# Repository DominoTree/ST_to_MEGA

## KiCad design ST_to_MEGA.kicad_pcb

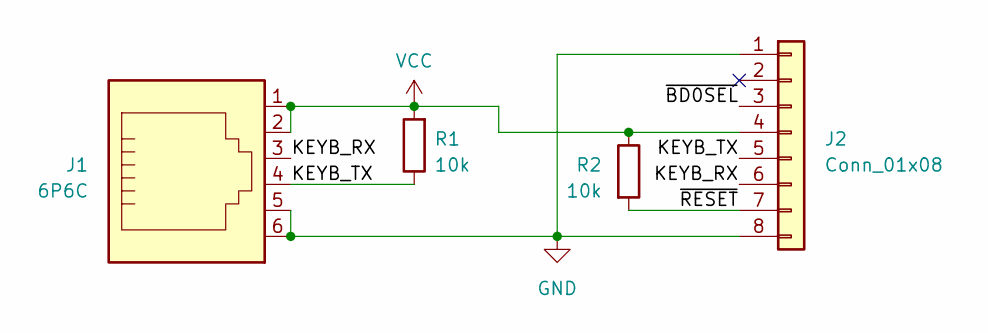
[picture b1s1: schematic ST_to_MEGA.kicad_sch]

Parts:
J1: 6P6C; RJ12_Amphenol_54601
J2: Conn_01x08; PinHeader_1x08_P2.54mm_Vertical
R1, R2: 10k; R_0603_1608Metric

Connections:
/KEYB_RX: J1.3, J2.6
/KEYB_TX: J1.4, J2.5, R1.1
/~BD0SEL: J2.3
/~RESET: J2.7, R2.2
GND: J1.5, J1.6, J2.1, J2.8
VCC: J1.1, J1.2, J2.4, R1.2, R2.1

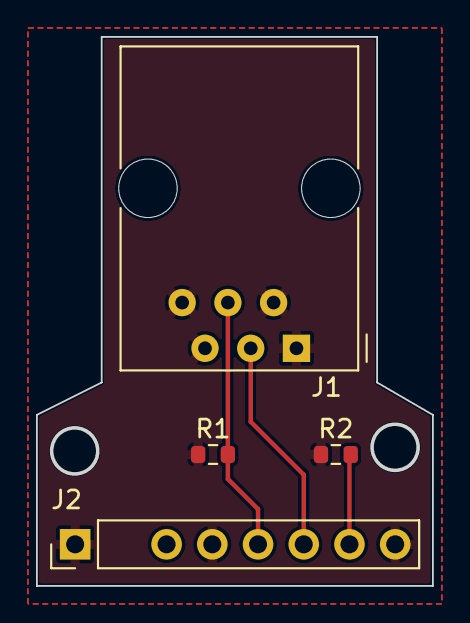
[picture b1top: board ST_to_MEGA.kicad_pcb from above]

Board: 2 copper layers, 21.9 x 30.4 mm, 4 parts (0 on the bottom side), 5 nets.

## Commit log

2021-06-04 init
